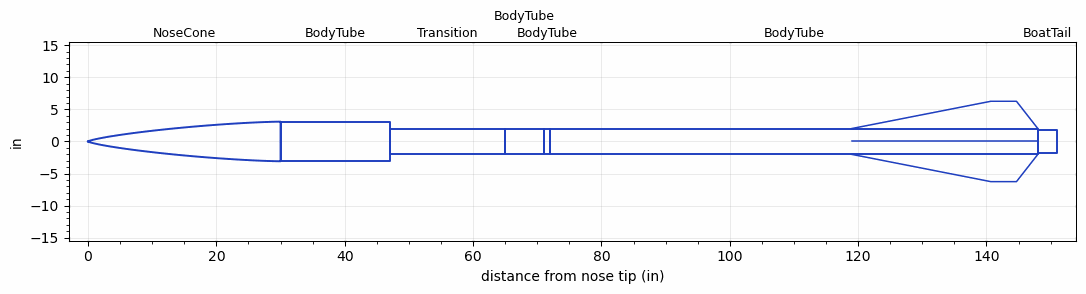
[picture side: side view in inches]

<RASAeroDocument>
 <FileVersion>2</FileVersion>
 <RocketDesign>
  <NoseCone>
   <Length>29.9999</Length>
   <Diameter>6.17</Diameter>
   <Shape>Von Karman Ogive</Shape>
   <Location>0</Location>
  </NoseCone>
  <BodyTube>
   <Length>17</Length>
   <Diameter>6.17</Diameter>
   <Location>29.9999</Location>
  </BodyTube>
  <Transition>
   <Length>18</Length>
   <Diameter>4.02</Diameter>
   <RearDiameter>4.02</RearDiameter>
   <Location>46.9999</Location>
  </Transition>
  <BodyTube>
   <Length>6</Length>
   <Diameter>4.02</Diameter>
   <Location>64.9999</Location>
  </BodyTube>
  <BodyTube>
   <Length>1</Length>
   <Diameter>4.02</Diameter>
   <Location>70.9999</Location>
  </BodyTube>
  <BodyTube>
   <Length>75.9998</Length>
   <Diameter>4.02</Diameter>
   <Location>71.9999</Location>
   <Fin>
    <Count>4</Count>
    <Chord>28.9999</Chord>
    <Span>4.25</Span>
    <SweepDistance>21.6717</SweepDistance>
    <TipChord>4</TipChord>
    <Thickness>0.1181</Thickness>
    <Location>28.9999</Location>
    <AirfoilSection>Square</AirfoilSection>
   </Fin>
  </BodyTube>
  <BoatTail>
   <Length>2.9528</Length>
   <Diameter>3.5</Diameter>
   <RearDiameter>3.5</RearDiameter>
   <Location>147.9997</Location>
  </BoatTail>
  <Surface>Rough Camouflage Paint</Surface>
  <CD>0</CD>
  <ModifiedBarrowman>False</ModifiedBarrowman>
  <Turbulence>False</Turbulence>
  <UseBooster1>False</UseBooster1>
  <UseBooster2>False</UseBooster2>
 </RocketDesign>
 <LaunchSite>
  <Altitude>0</Altitude>
  <Pressure>29.9214</Pressure>
  <RodAngle>0</RodAngle>
  <RodLength>39.37</RodLength>
  <Temperature>59</Temperature>
  <WindSpeed>4.4739</WindSpeed>
 </LaunchSite>
 <Recovery>
  <Altitude1>656.168</Altitude1>
  <Altitude2>0</Altitude2>
  <DeviceType1>Parachute</DeviceType1>
  <DeviceType2>None</DeviceType2>
  <Event1>True</Event1>
  <Event2>False</Event2>
  <Size1>47.9999</Size1>
  <Size2>0</Size2>
  <EventType1>Apogee</EventType1>
  <EventType2>None</EventType2>
  <CD1>2.2</CD1>
  <CD2>0</CD2>
 </Recovery>
 <SimulationList>
  <Simulation>
   <SustainerLaunchWt>63.7717</SustainerLaunchWt>
   <SustainerCG>96.2637</SustainerCG>
   <SustainerIgnitionDelay>0</SustainerIgnitionDelay>
   <Booster1SeparationDelay>0</Booster1SeparationDelay>
   <Booster1IgnitionDelay>0</Booster1IgnitionDelay>
   <IncludeBooster1>False</IncludeBooster1>
   <Booster2Delay>0</Booster2Delay>
   <IncludeBooster2>False</IncludeBooster2>
  </Simulation>
  <Simulation>
   <SustainerLaunchWt>62.8716</SustainerLaunchWt>
   <SustainerCG>96.7879</SustainerCG>
   <SustainerIgnitionDelay>0</SustainerIgnitionDelay>
   <Booster1SeparationDelay>0</Booster1SeparationDelay>
   <Booster1IgnitionDelay>0</Booster1IgnitionDelay>
   <IncludeBooster1>False</IncludeBooster1>
   <Booster2Delay>0</Booster2Delay>
   <IncludeBooster2>False</IncludeBooster2>
  </Simulation>
 </SimulationList>
</RASAeroDocument>
